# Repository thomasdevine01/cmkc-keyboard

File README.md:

# Chico State Mechanical Keyboard Club

<p align = "center">
    A 65% keyboard that features a rotary encoder, OLED Screen and Programmable Firmware.
</p>

## [Installation Guide](Docs/)
  
  1. [Foreword](https://github.com/thomasdevine01/cmkc-keyboard/blob/main/Docs/README.md#foreword)
  2. [Required Parts](https://github.com/thomasdevine01/cmkc-keyboard/blob/main/Docs/README.md#required-parts)
  3. [Optional parts](https://github.com/thomasdevine01/cmkc-keyboard/blob/main/Docs/README.md#optional-parts)
  4. [Tools](https://github.com/thomasdevine01/cmkc-keyboard/blob/main/Docs/README.md#tools)
  5. [Minimum requirements](https://github.com/thomasdevine01/cmkc-keyboard/blob/main/Docs/README.md#minimum-requirements)
  6. [Quality of Life Improvements](https://github.com/thomasdevine01/cmkc-keyboard/blob/main/Docs/README.md#quality-of-life-improvements)
  7. [PCBs: Quick Review](https://github.com/thomasdevine01/cmkc-keyboard/blob/main/Docs/README.md#pcbs-quick-review)
  8. [Soldering: Quick Review](https://github.com/thomasdevine01/cmkc-keyboard/blob/main/Docs/README.md#soldering-quick-review)
  9. [Soldering Tips](https://github.com/thomasdevine01/cmkc-keyboard/blob/main/Docs/README.md#soldering-tips)
  10. [PCB Assembly Tasks](https://github.com/thomasdevine01/cmkc-keyboard/blob/main/Docs/README.md#pcb-assembly-tasks)
  11. [Diodes](https://github.com/thomasdevine01/cmkc-keyboard/blob/main/Docs/README.md#diodes)
  12. [uC Socket](https://github.com/thomasdevine01/cmkc-keyboard/blob/main/Docs/README.md#uc-socket)
  13. [Hardware Fix - Tying Pin 9 to Pin 4](https://github.com/thomasdevine01/cmkc-keyboard/blob/main/Docs/README.md#hardware-fix---tying-pin-9-to-pin-4)
  14. [Recommended Fix - Top Layer](https://github.com/thomasdevine01/cmkc-keyboard/blob/main/Docs/README.md#recommended-fix---top-layer)
  15. [How I did it - Bottom layer underneath socket](https://github.com/thomasdevine01/cmkc-keyboard/blob/main/Docs/README.md#how-i-did-it---bottom-layer-underneath-socket)
  16. [uC header pins](https://github.com/thomasdevine01/cmkc-keyboard/blob/main/Docs/README.md#uc-header-pins)
  17. [Stabilizers](https://github.com/thomasdevine01/cmkc-keyboard/blob/main/Docs/README.md#stabilizers)
  18. [Assembling Stabilizers](https://github.com/thomasdevine01/cmkc-keyboard/blob/main/Docs/README.md#assembling-stabilizers)
  19. [Switches](https://github.com/thomasdevine01/cmkc-keyboard/blob/main/Docs/README.md#switches)
  20. [OLED](https://github.com/thomasdevine01/cmkc-keyboard/blob/main/Docs/README.md#oled)
  21. [Demultiplexer](https://github.com/thomasdevine01/cmkc-keyboard/blob/main/Docs/README.md#demultiplexer)
  22. [Rotary Encoder](https://github.com/thomasdevine01/cmkc-keyboard/blob/main/Docs/README.md#rotary-encoder)
  23. [Soldering Sanity Check](https://github.com/thomasdevine01/cmkc-keyboard/blob/main/Docs/README.md#soldering-sanity-check)
  
## [Photo Gallery](Docs/Images)
## [Parts](Docs/)
### Credits

- Circuit-Dude
- Thomas Devine 

### [Sources](Docs/Sources/)

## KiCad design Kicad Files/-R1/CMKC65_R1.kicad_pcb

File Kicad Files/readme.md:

These are the Schematic and PCB Layout files for the CMKC-65% keyboard.

The current board revision is the -R1.

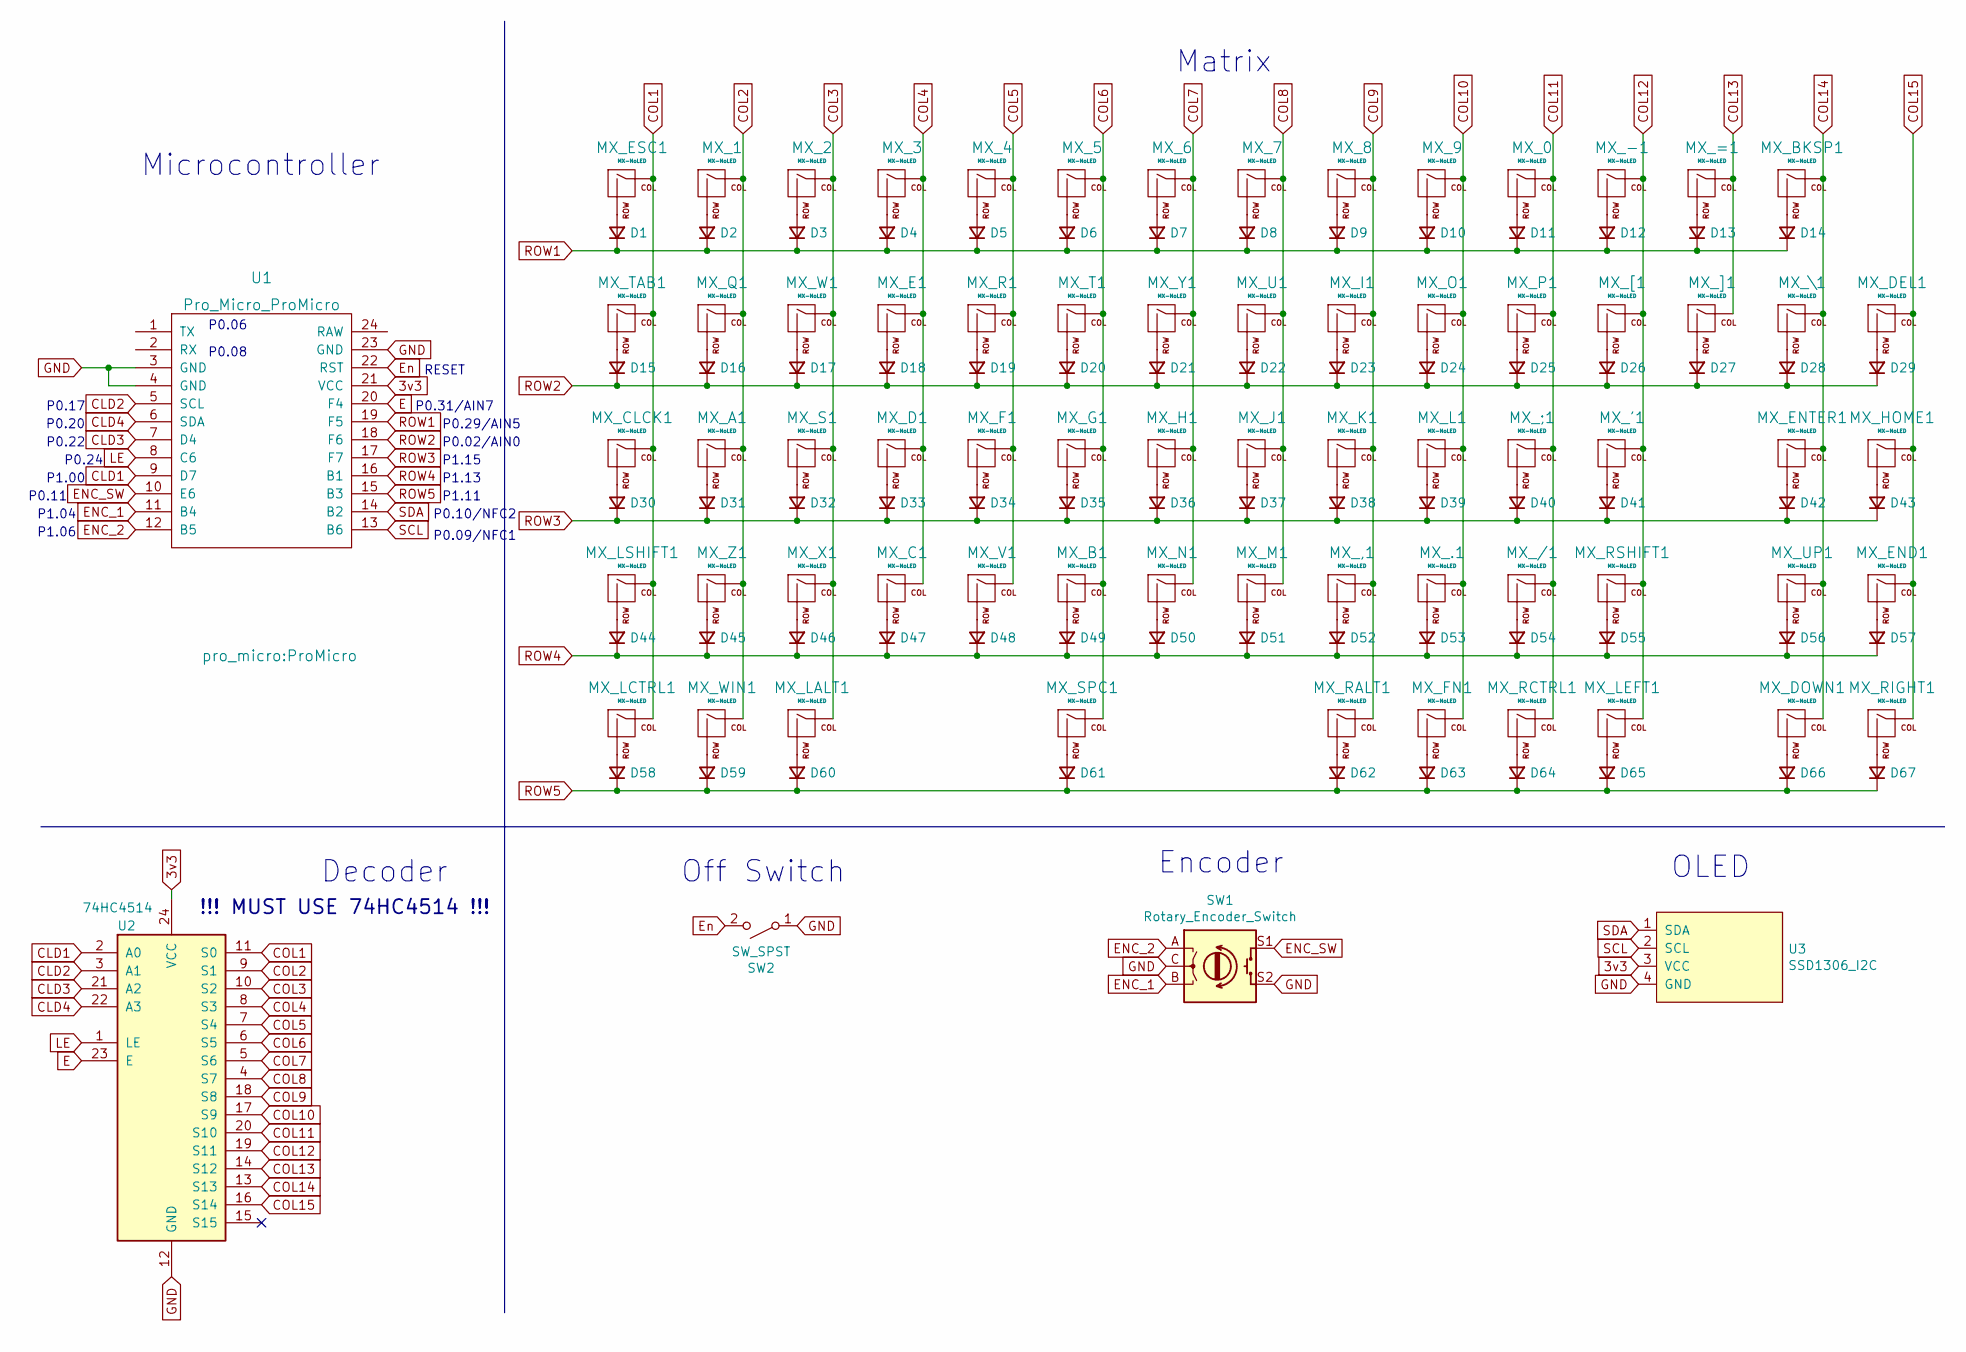
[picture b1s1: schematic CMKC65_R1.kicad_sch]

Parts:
D1, D2, D3, D4, D5, D6, D7, D8, D9, D10, D11, D12, D13, D14, D15, D16, D17, D18, D19, D20, D21, D22, D23, D24, D25, D26, D27, D28, D29, D30, D31, D32, D33, D34, D35, D36, D37, D38, D39, D40, D41, D42, D43, D44, D45, D46, D47, D48, D49, D50, D51, D52, D53, D54, D55, D56, D57, D58, D59, D60, D61, D62, D63, D64, D65, D66, D67: D_Small; D_DO-35_SOD27_P7.62mm_Horizontal
MX_0, MX_1, MX_2, MX_3, MX_4, MX_5, MX_6, MX_7, MX_8, MX_9, MX_.1: MX-NoLED; MXOnly-1U-NoLED
MX_'1: MX-NoLED; MXOnly-1U-NoLED
MX_,1: MX-NoLED; MXOnly-1U-NoLED
MX_-1: MX-NoLED; MXOnly-1U-NoLED
MX_/1: MX-NoLED; MXOnly-1U-NoLED
MX_;1: MX-NoLED; MXOnly-1U-NoLED
MX_=1: MX-NoLED; MXOnly-1U-NoLED
MX_A1: MX-NoLED; MXOnly-1U-NoLED
MX_B1: MX-NoLED; MXOnly-1U-NoLED
MX_BKSP1: MX-NoLED; MXOnly-2U-NoLED
MX_C1: MX-NoLED; MXOnly-1U-NoLED
MX_CLCK1: MX-NoLED; MXOnly-1.75U-NoLED
MX_D1: MX-NoLED; MXOnly-1U-NoLED
MX_DEL1: MX-NoLED; MXOnly-1U-NoLED
MX_DOWN1: MX-NoLED; MXOnly-1U-NoLED
MX_E1: MX-NoLED; MXOnly-1U-NoLED
MX_END1: MX-NoLED; MXOnly-1U-NoLED
MX_ENTER1: MX-NoLED; MXOnly-2.25U-NoLED
MX_ESC1: MX-NoLED; MXOnly-1U-NoLED
MX_F1: MX-NoLED; MXOnly-1U-NoLED
MX_FN1: MX-NoLED; MXOnly-1U-NoLED
MX_G1: MX-NoLED; MXOnly-1U-NoLED
MX_H1: MX-NoLED; MXOnly-1U-NoLED
MX_HOME1: MX-NoLED; MXOnly-1U-NoLED
MX_I1: MX-NoLED; MXOnly-1U-NoLED
MX_J1: MX-NoLED; MXOnly-1U-NoLED
MX_K1: MX-NoLED; MXOnly-1U-NoLED
MX_L1: MX-NoLED; MXOnly-1U-NoLED
MX_LALT1: MX-NoLED; MXOnly-1.25U-NoLED
MX_LCTRL1: MX-NoLED; MXOnly-1.25U-NoLED
MX_LEFT1: MX-NoLED; MXOnly-1U-NoLED
MX_LSHIFT1: MX-NoLED; MXOnly-2.25U-NoLED
MX_M1: MX-NoLED; MXOnly-1U-NoLED
MX_N1: MX-NoLED; MXOnly-1U-NoLED
MX_O1: MX-NoLED; MXOnly-1U-NoLED
MX_P1: MX-NoLED; MXOnly-1U-NoLED
MX_Q1: MX-NoLED; MXOnly-1U-NoLED
MX_R1: MX-NoLED; MXOnly-1U-NoLED
MX_RALT1: MX-NoLED; MXOnly-1U-NoLED
MX_RCTRL1: MX-NoLED; MXOnly-1U-NoLED
MX_RIGHT1: MX-NoLED; MXOnly-1U-NoLED
MX_RSHIFT1: MX-NoLED; MXOnly-1.75U-NoLED
MX_S1: MX-NoLED; MXOnly-1U-NoLED
MX_SPC1: MX-NoLED; MXOnly-6.25U-ReversedStabilizers-NoLED
MX_T1: MX-NoLED; MXOnly-1U-NoLED
MX_TAB1: MX-NoLED; MXOnly-1.5U-NoLED
MX_U1: MX-NoLED; MXOnly-1U-NoLED
MX_UP1: MX-NoLED; MXOnly-1U-NoLED
MX_V1: MX-NoLED; MXOnly-1U-NoLED
MX_W1: MX-NoLED; MXOnly-1U-NoLED
MX_WIN1: MX-NoLED; MXOnly-1.25U-NoLED
MX_X1: MX-NoLED; MXOnly-1U-NoLED
MX_Y1: MX-NoLED; MXOnly-1U-NoLED
MX_Z1: MX-NoLED; MXOnly-1U-NoLED
MX_[1: MX-NoLED; MXOnly-1U-NoLED
MX_\1: MX-NoLED; MXOnly-1.5U-NoLED
MX_]1: MX-NoLED; MXOnly-1U-NoLED
SW1: Rotary_Encoder_Switch; RotaryEncoder_Alps_EC11E-Switch_Vertical_H20mm
SW2: SW_SPST; SW_PUSH_6mm
U1: Pro_Micro_ProMicro; ProMicro
U2: 74HC4514; SOIC-24W_7.5x15.4mm_P1.27mm
U3: SSD1306_I2C; OLED

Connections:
3v3: U1.21 (VCC), U2.24 (VCC), U3.3 (VCC)
CLD1: U1.9 (D7), U2.2 (A0)
CLD2: U1.5 (SCL), U2.3 (A1)
CLD3: U1.7 (D4), U2.21 (A2)
CLD4: U1.6 (SDA), U2.22 (A3)
COL1: MX_CLCK1.1 (COL), MX_ESC1.1 (COL), MX_LCTRL1.1 (COL), MX_LSHIFT1.1 (COL), MX_TAB1.1 (COL), U2.11 (S0)
COL2: MX_1.1 (COL), MX_A1.1 (COL), MX_Q1.1 (COL), MX_WIN1.1 (COL), MX_Z1.1 (COL), U2.9 (S1)
COL3: MX_2.1 (COL), MX_LALT1.1 (COL), MX_S1.1 (COL), MX_W1.1 (COL), MX_X1.1 (COL), U2.10 (S2)
COL4: MX_3.1 (COL), MX_C1.1 (COL), MX_D1.1 (COL), MX_E1.1 (COL), U2.8 (S3)
COL5: MX_4.1 (COL), MX_F1.1 (COL), MX_R1.1 (COL), MX_V1.1 (COL), U2.7 (S4)
COL6: MX_5.1 (COL), MX_B1.1 (COL), MX_G1.1 (COL), MX_SPC1.1 (COL), MX_T1.1 (COL), U2.6 (S5)
COL7: MX_6.1 (COL), MX_H1.1 (COL), MX_N1.1 (COL), MX_Y1.1 (COL), U2.5 (S6)
COL8: MX_7.1 (COL), MX_J1.1 (COL), MX_M1.1 (COL), MX_U1.1 (COL), U2.4 (S7)
COL9: MX_8.1 (COL), MX_,1.1 (COL), MX_I1.1 (COL), MX_K1.1 (COL), MX_RALT1.1 (COL), U2.18 (S8)
COL10: MX_9.1 (COL), MX_.1.1 (COL), MX_FN1.1 (COL), MX_L1.1 (COL), MX_O1.1 (COL), U2.17 (S9)
COL11: MX_0.1 (COL), MX_/1.1 (COL), MX_;1.1 (COL), MX_P1.1 (COL), MX_RCTRL1.1 (COL), U2.20 (S10)
COL12: MX_'1.1 (COL), MX_-1.1 (COL), MX_LEFT1.1 (COL), MX_RSHIFT1.1 (COL), MX_[1.1 (COL), U2.19 (S11)
COL13: MX_=1.1 (COL), MX_]1.1 (COL), U2.14 (S12)
COL14: MX_BKSP1.1 (COL), MX_DOWN1.1 (COL), MX_ENTER1.1 (COL), MX_UP1.1 (COL), MX_\1.1 (COL), U2.13 (S13)
COL15: MX_DEL1.1 (COL), MX_END1.1 (COL), MX_HOME1.1 (COL), MX_RIGHT1.1 (COL), U2.16 (S14)
E: U1.20 (F4), U2.23 (E)
ENC_1: SW1.B, U1.11 (B4)
ENC_2: SW1.A, U1.12 (B5)
ENC_SW: SW1.S1, U1.10 (E6)
En: SW2.2 (B), U1.22 (RST)
GND: SW1.C, SW1.S2, SW2.1 (A), U1.3 (GND), U1.4 (GND), U1.23 (GND), U2.12 (GND), U3.4 (GND)
LE: U1.8 (C6), U2.1 (LE)
unnamed: D1.2 (A), MX_ESC1.2 (ROW)
unnamed: D2.2 (A), MX_1.2 (ROW)
unnamed: D3.2 (A), MX_2.2 (ROW)
unnamed: D4.2 (A), MX_3.2 (ROW)
unnamed: D5.2 (A), MX_4.2 (ROW)
unnamed: D6.2 (A), MX_5.2 (ROW)
unnamed: D7.2 (A), MX_6.2 (ROW)
unnamed: D8.2 (A), MX_7.2 (ROW)
unnamed: D9.2 (A), MX_8.2 (ROW)
unnamed: D10.2 (A), MX_9.2 (ROW)
unnamed: D11.2 (A), MX_0.2 (ROW)
unnamed: D12.2 (A), MX_-1.2 (ROW)
unnamed: D13.2 (A), MX_=1.2 (ROW)
unnamed: D14.2 (A), MX_BKSP1.2 (ROW)
unnamed: D15.2 (A), MX_TAB1.2 (ROW)
unnamed: D16.2 (A), MX_Q1.2 (ROW)
unnamed: D17.2 (A), MX_W1.2 (ROW)
unnamed: D18.2 (A), MX_E1.2 (ROW)
unnamed: D19.2 (A), MX_R1.2 (ROW)
unnamed: D20.2 (A), MX_T1.2 (ROW)
unnamed: D21.2 (A), MX_Y1.2 (ROW)
unnamed: D22.2 (A), MX_U1.2 (ROW)
unnamed: D23.2 (A), MX_I1.2 (ROW)
unnamed: D24.2 (A), MX_O1.2 (ROW)
unnamed: D25.2 (A), MX_P1.2 (ROW)
unnamed: D26.2 (A), MX_[1.2 (ROW)
unnamed: D27.2 (A), MX_]1.2 (ROW)
unnamed: D28.2 (A), MX_\1.2 (ROW)
unnamed: D29.2 (A), MX_DEL1.2 (ROW)
unnamed: D30.2 (A), MX_CLCK1.2 (ROW)
unnamed: D31.2 (A), MX_A1.2 (ROW)
unnamed: D32.2 (A), MX_S1.2 (ROW)
unnamed: D33.2 (A), MX_D1.2 (ROW)
unnamed: D34.2 (A), MX_F1.2 (ROW)
unnamed: D35.2 (A), MX_G1.2 (ROW)
unnamed: D36.2 (A), MX_H1.2 (ROW)
unnamed: D37.2 (A), MX_J1.2 (ROW)
unnamed: D38.2 (A), MX_K1.2 (ROW)
unnamed: D39.2 (A), MX_L1.2 (ROW)
unnamed: D40.2 (A), MX_;1.2 (ROW)
unnamed: D41.2 (A), MX_'1.2 (ROW)
unnamed: D42.2 (A), MX_ENTER1.2 (ROW)
unnamed: D43.2 (A), MX_HOME1.2 (ROW)
unnamed: D44.2 (A), MX_LSHIFT1.2 (ROW)
unnamed: D45.2 (A), MX_Z1.2 (ROW)
unnamed: D46.2 (A), MX_X1.2 (ROW)
unnamed: D47.2 (A), MX_C1.2 (ROW)
unnamed: D48.2 (A), MX_V1.2 (ROW)
unnamed: D49.2 (A), MX_B1.2 (ROW)
unnamed: D50.2 (A), MX_N1.2 (ROW)
unnamed: D51.2 (A), MX_M1.2 (ROW)
unnamed: D52.2 (A), MX_,1.2 (ROW)
unnamed: D53.2 (A), MX_.1.2 (ROW)
unnamed: D54.2 (A), MX_/1.2 (ROW)
unnamed: D55.2 (A), MX_RSHIFT1.2 (ROW)
unnamed: D56.2 (A), MX_UP1.2 (ROW)
unnamed: D57.2 (A), MX_END1.2 (ROW)
unnamed: D58.2 (A), MX_LCTRL1.2 (ROW)
unnamed: D59.2 (A), MX_WIN1.2 (ROW)
unnamed: D60.2 (A), MX_LALT1.2 (ROW)
unnamed: D61.2 (A), MX_SPC1.2 (ROW)
unnamed: D62.2 (A), MX_RALT1.2 (ROW)
unnamed: D63.2 (A), MX_FN1.2 (ROW)
unnamed: D64.2 (A), MX_RCTRL1.2 (ROW)
unnamed: D65.2 (A), MX_LEFT1.2 (ROW)
unnamed: D66.2 (A), MX_DOWN1.2 (ROW)
unnamed: D67.2 (A), MX_RIGHT1.2 (ROW)
ROW1: D1.1 (K), D2.1 (K), D3.1 (K), D4.1 (K), D5.1 (K), D6.1 (K), D7.1 (K), D8.1 (K), D9.1 (K), D10.1 (K), D11.1 (K), D12.1 (K), D13.1 (K), D14.1 (K), U1.19 (F5)
ROW2: D15.1 (K), D16.1 (K), D17.1 (K), D18.1 (K), D19.1 (K), D20.1 (K), D21.1 (K), D22.1 (K), D23.1 (K), D24.1 (K), D25.1 (K), D26.1 (K), D27.1 (K), D28.1 (K), D29.1 (K), U1.18 (F6)
ROW3: D30.1 (K), D31.1 (K), D32.1 (K), D33.1 (K), D34.1 (K), D35.1 (K), D36.1 (K), D37.1 (K), D38.1 (K), D39.1 (K), D40.1 (K), D41.1 (K), D42.1 (K), D43.1 (K), U1.17 (F7)
ROW4: D44.1 (K), D45.1 (K), D46.1 (K), D47.1 (K), D48.1 (K), D49.1 (K), D50.1 (K), D51.1 (K), D52.1 (K), D53.1 (K), D54.1 (K), D55.1 (K), D56.1 (K), D57.1 (K), U1.16 (B1)
ROW5: D58.1 (K), D59.1 (K), D60.1 (K), D61.1 (K), D62.1 (K), D63.1 (K), D64.1 (K), D65.1 (K), D66.1 (K), D67.1 (K), U1.15 (B3)
SCL: U1.13 (B6), U3.2 (SCL)
SDA: U1.14 (B2), U3.1 (SDA)

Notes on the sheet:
P0.20
P0.08
P0.24
P0.29/AIN5
!!! MUST USE 74HC4514 !!!
Decoder
P1.06
P1.11
P0.31/AIN7
Microcontroller
P0.06
P0.22
Off Switch
P1.00
P0.02/AIN0
OLED
P0.10/NFC2
Matrix
P0.09/NFC1
P1.04
P0.11
RESET
Encoder
P1.13
P1.15
P0.17

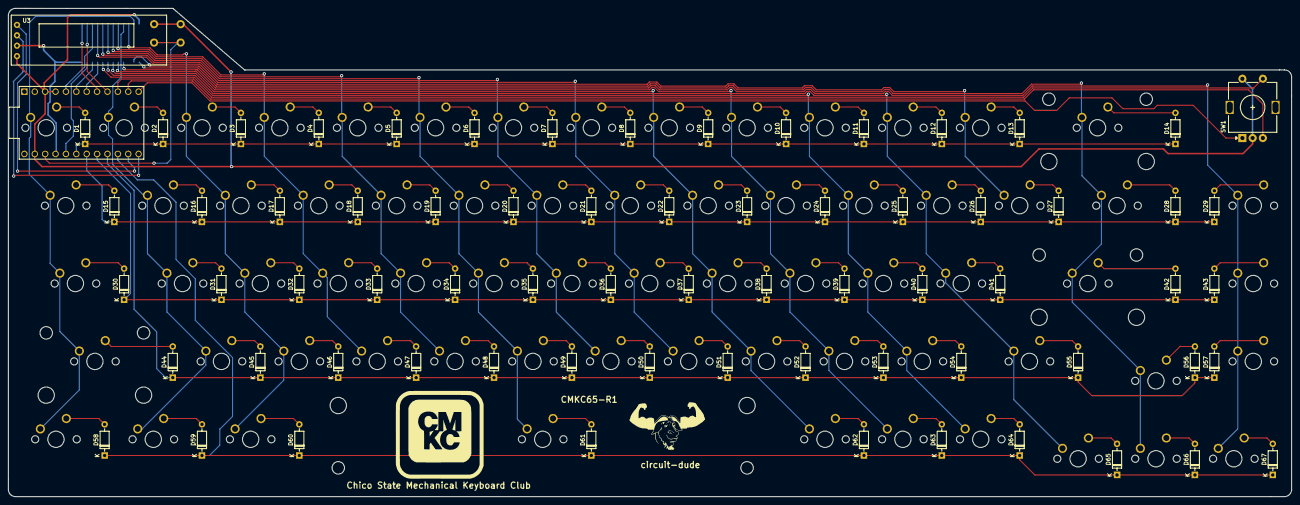
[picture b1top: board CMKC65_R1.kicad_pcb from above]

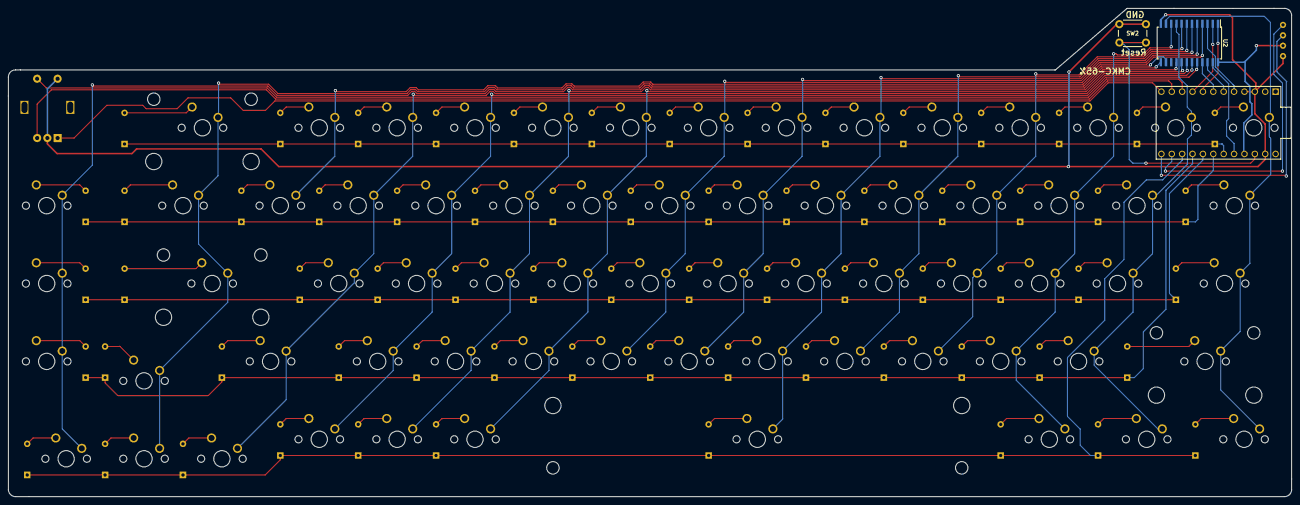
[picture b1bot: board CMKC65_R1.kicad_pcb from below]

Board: 2 copper layers, 313.9 x 119.4 mm, 141 parts (3 on the bottom side), 101 nets.

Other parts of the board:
Chico State Mechanical Keyboard Club: LOGO
circuit-dude: LOGO

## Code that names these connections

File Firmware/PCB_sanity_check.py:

#==================================
# This code is meant to be a sanity check after assembling the circuits on the PCB.
# and flashing the uC. We can check that every button is "seen" when we press it.
#==================================

print("Hello World!")

import board
import digitalio
import time


from digitalio import DigitalInOut, Direction, Pull




#==================================
# E and LE pins
#==================================
    #LE needs to be high
    #E needs to be low
LE = digitalio.DigitalInOut(board.P0_24)
LE.direction = digitalio.Direction.OUTPUT
LE.value = 1

E = digitalio.DigitalInOut(board.P0_31)
E.direction = digitalio.Direction.OUTPUT
E.value = 0

#==================================
# CLD pins
#==================================
CLD1 = digitalio.DigitalInOut(board.P1_00)
CLD1.direction = digitalio.Direction.OUTPUT
CLD1.value = 0

CLD2 = digitalio.DigitalInOut(board.P0_17)
CLD2.direction = digitalio.Direction.OUTPUT
CLD2.value = 0

CLD3 = digitalio.DigitalInOut(board.P0_22)
CLD3.direction = digitalio.Direction.OUTPUT
CLD3.value = 0

CLD4 = digitalio.DigitalInOut(board.P0_20)
CLD4.direction = digitalio.Direction.OUTPUT
CLD4.value = 0

#==================================
# ROW pins
#==================================
ROW1 = digitalio.DigitalInOut(board.P0_29)
ROW1.direction = digitalio.Direction.INPUT
ROW1.pull = Pull.DOWN

ROW2 = digitalio.DigitalInOut(board.P0_02)
ROW2.direction = digitalio.Direction.INPUT
ROW2.pull = Pull.DOWN

ROW3 = digitalio.DigitalInOut(board.P1_15)
ROW3.direction = digitalio.Direction.INPUT
ROW3.pull = Pull.DOWN

ROW4 = digitalio.DigitalInOut(board.P1_13)
ROW4.direction = digitalio.Direction.INPUT
ROW4.pull = Pull.DOWN

ROW5 = digitalio.DigitalInOut(board.P1_11)
ROW5.direction = digitalio.Direction.INPUT
ROW5.pull = Pull.DOWN


print(dir(board))  #shows all pins names on uC


cols = [CLD1, CLD2, CLD3, CLD4]
rows = [ROW1, ROW2, ROW3, ROW4, ROW5]


#reset columns
for i in range(3):
    cols[i].value = 0
    print("i is", i)
    




while True:

# this looks stupid, but we need to toggle every "bit" in our "cols" variable so that we can count from 0-14 in binary.
# State machine looks like: select column, check all rows, tell us which button is pressed based on col,row 
    for d in range(2): #bit 3
        cols[3].value = d
        for c in range(2): #bit 2
            cols[2].value = c
            for b in range(2): #bit 1
                cols[1].value = b
                for a in range(2): #bit 0
                    cols[0].value = a
                    for j in range(5):
                        if rows[j].value:
                            col = ((8*d) + (4*c) + (2*b )+ a)
                            print("Button column: ", col, ", row: ", j, " pressed")
                            time.sleep(0.1)

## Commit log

2023-03-09 Adding work done to import NICE!-nano
    This is the work done to modify the existing 65% mechanical keyboard design from Nicell/Dissatisfaction-65.
    Not exactly sure what needs to be added in order for the project to work correctly, hopefully all the libraries aren't broken after this commit.
    Work done includes:
    - schematic changes to support NICE!-nano uC - pin selections we're chosen at random. changing pin selections may lead to an easier time routing but this was mostly for a first pass/sanity check when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
    -Note on the footprint, the footprint was leveraged from an existing design, mkdl/Unix60. The footprint was saved from the project's PCB and added to a
2023-03-11 updated references
2023-03-13 Placed NICE!-nano such that the micro usb comes right up to the edge of the board re-routed a bunch of column signals, the rotary encoder signals, reset switch, rotary encoder push button switch, 3v3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
2023-03-20 adding gerbers
2023-05-07 updated readme to contain framework for guide
2023-09-28 Added Firmware for Testing
2023-09-28 Removed submodule from 'firmware'
2023-09-28 adding some sanity check code to the firmware repo. The essentially performs a keyboard matrix scan and prints back to the user which button was pressed in terms of rows and columns.
    This is meant to allow people to check that everything is working correctly after PCB assembly and flashing the board. If you can't hit every key on your keyboard and see the correct button press (or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
2023-09-28 adding schematic pdf for people without KiCad
    I also changed the scheamtic to reflect the known hardware issue where CLD1 was connected to PIN4. PIN4 is a straight up GND pin on the uC. So far this addresses the issues with the schematic. LAYOUT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
2023-09-28 Moved Kicad files from root to separate folder
2023-09-28 Added .gitignore to clean up temp files
2023-09-28 Delete .DS_Store
    DS Store is a weird mac thing, I added it to the gitignore so we won't have this issue again
2023-09-30 Adding updated schematic. This is the scheamtic I used to generate the pdf with an addition bold comment by the decoder that we must use the 74HC4514
2023-10-04 Update README.md
    added discord to readme
2023-10-06 Added Docs Section
2023-10-07 firmware
2023-10-07 edited main readme
2023-10-08 Table of contents added to assembly guide
2023-10-08 added pictures to readme
2023-10-08 pictures added to doc readme
2023-10-08 added pictures to assembly guide readme
2023-10-08 Added main.py, kmk_keyboard.py and tidied Firmware/ Folder
2023-10-08 Create LICENSE
2023-10-08 Github pages setup and deployment
    sources
    Update README.md
    added icon
    Update _config.yml
    renamed files
    dark mode testing
2023-10-08 removed duplicate sections
2023-10-08 separated pages content
2023-10-08 new branch testing
2023-10-09 edited readme
2023-10-09 formatting changes
2023-10-09 new nav footer
2023-10-09 fixed typo
2023-10-10 Restructured Kicad Files Directory
    Added new -R1 folder. I'm not sure how we want to archive but this is how I'm used to.
    Deleted a bunch of bloat
    updated layout to fix the pin 4 - pin 9 problem on the uC socket.
    Added different reset switch, 6mm x 6mm push buttons are much more common
    added reset and gnd silkscreen for people who don't install a pushbutton for reset
    added CMKC-65% silkscreen to top side of board by OLED. This should be visible in the corner when assembled
2023-10-10 update readme for Kicad Folder
2023-10-10 update gerbers with new -R1 gerbers
2023-10-10 Restructured Kicad FIles, Updated README.md, update gerbers with new -R1 gerbers
    Restructured Kicad Files Directory
    Added new -R1 folder. I'm not sure how we want to archive but this is how I'm used to.
    Deleted a bunch of bloat
    updated layout to fix the pin 4 - pin 9 problem on the uC socket.
    Added different reset switch, 6mm x 6mm push buttons are much more common
    added reset and gnd silkscreen for people who don't install a pushbutton for reset
2023-10-10 Create CNAME
2023-10-11 removed _
2023-10-11 Revert "update"
    This reverts commit fd641436f3351521761f608cdb0c02345ece5042.
2023-10-14 nav bar edits
2023-10-14 navbar edits
2023-10-14 fix broken links
2023-10-14 formatting
